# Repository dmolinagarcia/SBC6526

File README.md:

# SBC6526

SBC6526 is a single board computer built around A 65c02 CPU. It has been designed with a very specific purpose, that has defined both its name and its specs. I've been working for some time already on a MOS6526 (The famous CIA used in Commodore Computers) replica using 74xx logic series ICs. Testing was done on a real C64, but soon this prove to be a very limiting factor. So I begin working on a small SBC, designed entirely around the 6526, that should allow me to run as many tests, with no limitations at all.

The initial set of requisites was

* Continuosly variable clock, from 1MHz to as far as possible, in order to push my replica to its limits
* Clock Frequency Display. Useful, and should look very cool.
* No input at all. Program the ROM (more on this later) and just run a suite of tests for the 6526.
* Basic output.. Something like a 20x4 Character LCD will do.
* Easy, quick, and on board ROM programming. I will be modifiying the code continuosly, so this is very important.
* Include a 6522. Why not!? It can also be useful for the tests
* Include a socket for a 6526. Compatibility with old NMOS 6526 is not needed, although it would be nice.
* Allow testing of all 6526 pins. Ports, serial, /FLAG interrupt, etc
* Independent reset for 6526.

SBCv1 came to life, fulfilling this requirements. Howeever, after using it for some time, it show some weakness. SBCv1 has a 6522 and a 6526. A 4x40 LCD is used as display, driven by the 6526. This causes the display to blank when running some tests, and sometimes, crashed the LCD into an unrecoverable state, that requires a complete power down. This along some layout issues, forced the next revision. 

## Memory Map

0000 - 7FFF RAM
8000 - 87FF I/O BANK 0 - FREE
8800 - 8FFF I/O BANK 1 - CIA1
9000 - 97FF I/O BANK 2 - VIA
9800 - 9FFF I/O BANK 3 - CIAEXT
A000 - A7FF I/O BANK 4
A800 - AFFF I/O BANK 5
B000 - B7FF I/O BANK 6
B800 - BFFF I/O BANK 7
C000 - FFFF RAM

# v2
Being my first attempt at creating a SBC, v1 had many flaws. There were some pull-up resistors missing, the PCB layout was a mess, the bootstrap code was... well... unreadable to be honest. Moreover, the CAD tool I choose for v1, Eagle Cad, has a nasty licensing which is pulling away many users. I decided to make the transition to KiCAD for the v2. It's still a work in progress, and completely untested, but feel free to take a look if you like.

SBCv2 adds a second 6526. There's a 40 pin DIP socket that accepts both a MOS6526 or any modern replacement. Second 6526 connects over a 40 pin IDC that matches the 74HCT6526 interface. The LCD is now driven by the 6522, so both 6526 are 100% usable for testing. 

On SBCv1, TOD in the 6526 was used to determine clock speed. Now, a 60hz signal generated by the arduino goes into the 6522 for this purpose. SBC6526 can now startup and run with no 6526 connected at all. 

## BootStrap

The SBC6526 has no ROM. RAM exists between 0000-7FFF and C000-FFFF. As you know, the 6502 CPU needs the startup vectors to be present in the last segment of memory so, how does the SBC6526 boot?

An Arduino NANO handles the startup sequence. On startup, it brings BE low, disconnecting the 6502 from the address and data busses, and the R/W line. This also enables a pair of 8bit shift registers that handle from now on the address bus.

The RAM IC has 2 enable inputs. One is controled via the SBC Address Decoding logic, the other, directly by the ARDUINO. During BootStraping, RAMCE pulses with PHI2 (independent from the arduino) and the Arduino pulses CE line. This is a bit unorthodox and may cause some failures to write, if the arduino pulse happens when PHI2 is  high. This is handled by trying several times to write.

When the ROM image is written, BE is released, and the 6502 is resetted by the Arduino itself.

## KiCAD

Full schematic and PCB. The migration from EagleCAD to KiCAD has not been easy, as I was very much used to EagleCad. But the change as been worth the effort. 

## Firmware

With little architectural changes from v1, original firmware will need just some minor changes. Most important one, LCD screen is now driven by the 6522 instead of the 6526. Also, the internal clock measurement has to be done also with the 6522. Memory map will be the same, with just a second CIA added into an empty IO Slot.

## RamFlasher

Java code to upload memory image to SBC

## Changelog

### Unreleased

* Nothing

### v2.0.2 12-01-2022

* Minor fixes to routing
* Right VCC hole was slightly offset. Fixed
* Removed /CE from arduino to RAM. As RAMCE pulses with PHI, it's not necessary, and we leave /CE tied to GND.
* Fixed RAM footprint, as it was too wide. Improved routing.
* Added current limiting resistor to LCD Contrast
* Bootstrap and Firmware published. Not completed, but working.

### v2.0.1 29-12-2021

* Fixed a bug on LCD frequency meter footprint. Top row pads were reversed
* First draft of firmware, only for LOGISIM version
* Initial draft of bootstrap loader. Still not working.

### v2.0.0 10-19-2021

* First v2 release
* First PCB run

### v1.0.0 xx-xx-2020

* First and last v1 release
* It works, which is enough.

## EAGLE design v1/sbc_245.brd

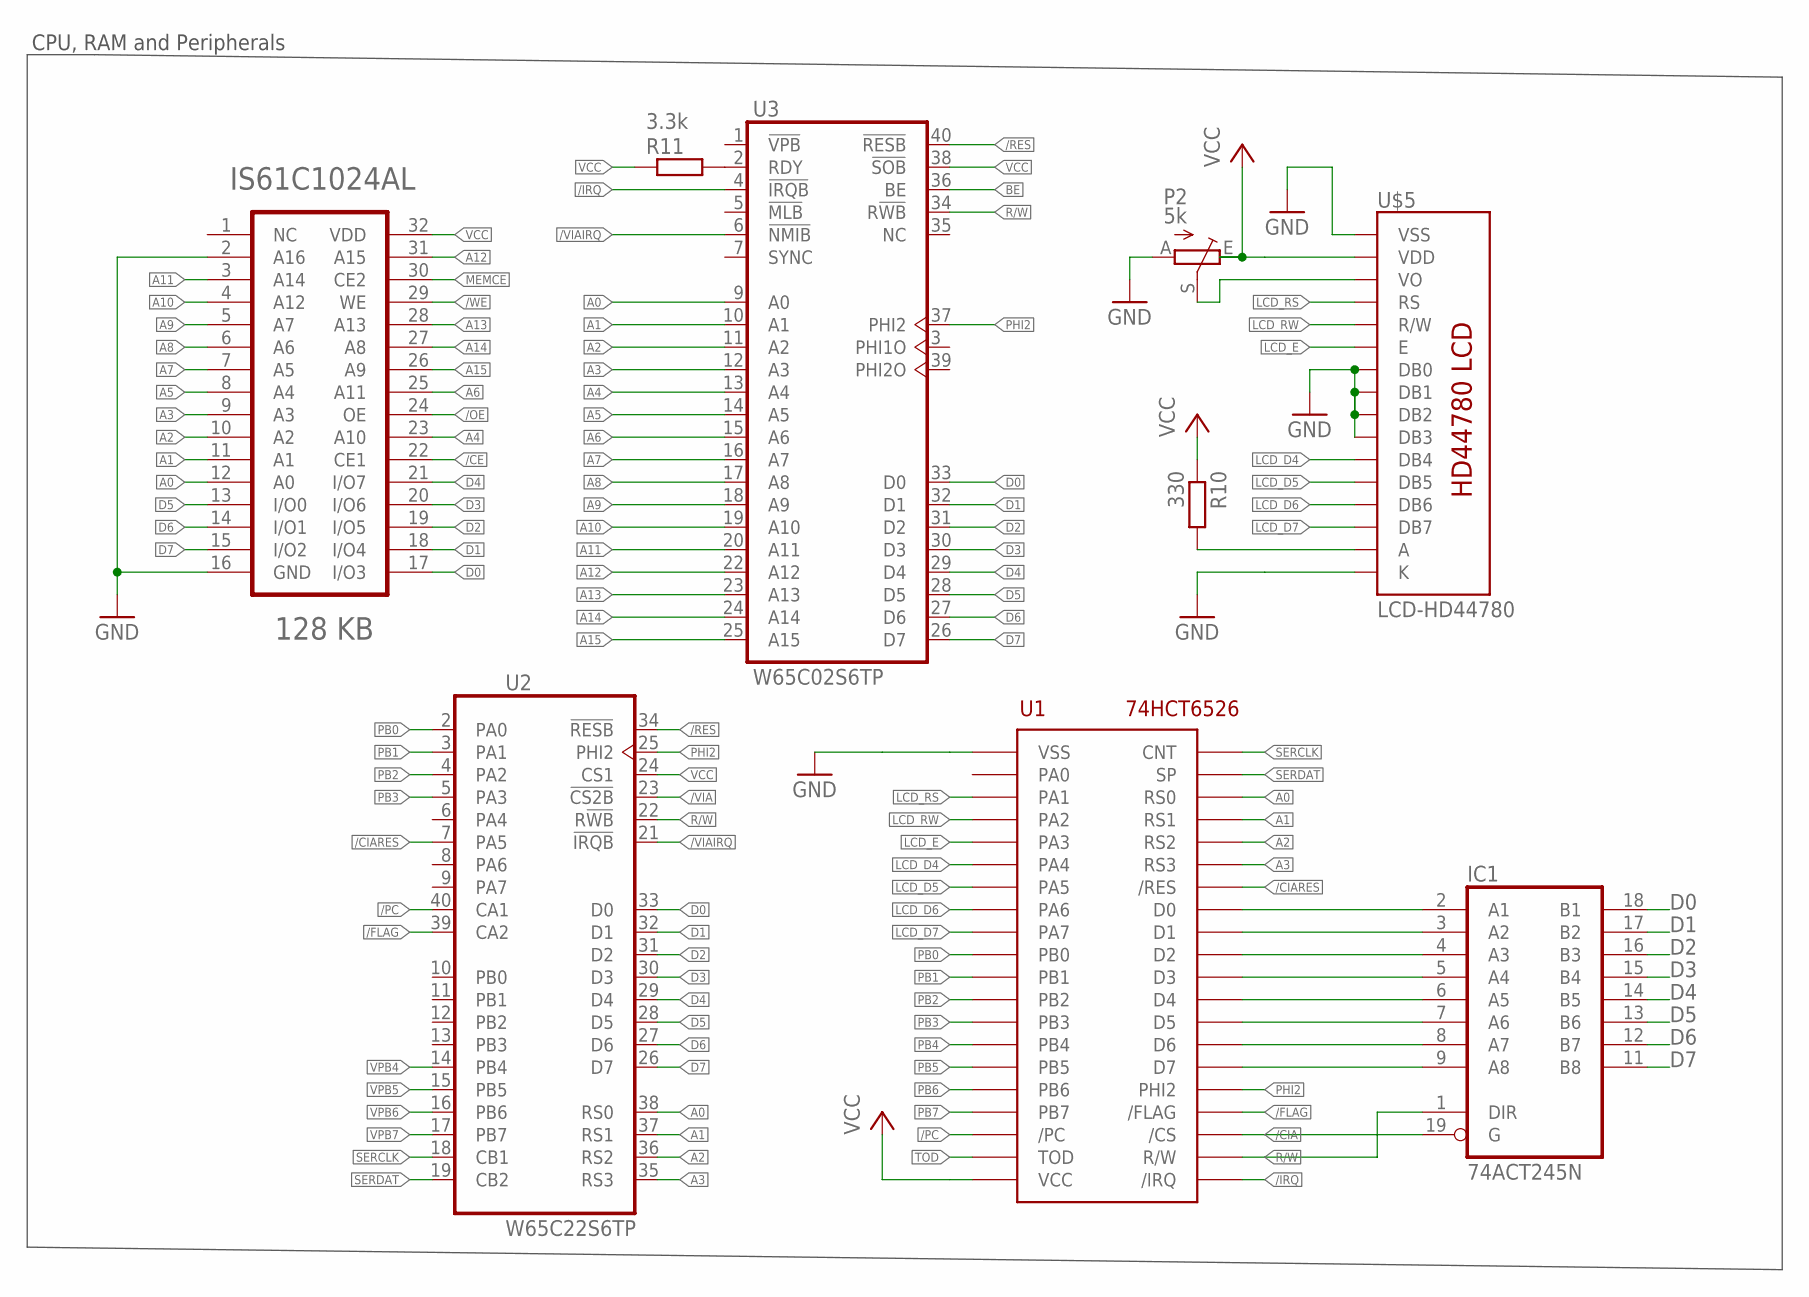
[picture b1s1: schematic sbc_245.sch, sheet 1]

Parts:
IC1: 74ACT245N; DIL20
P2: 5k; B64Y
R10: 330; R0805
R11: 3.3k; R0805
U1: 74HCT6526; DIP40
U2: W65C22S6TP; DIL40
U3: W65C02S6TP; DIL40
U4: IS61C1024AL-12JLI-TR; SOJ32/3
U$5: LCD-HD44780; LCD-20X4-4HOLES2X8

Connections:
/CE: U4.22 (CE1); also elsewhere on the board
/CIA: IC1.19 (G), U1.23 (/CS); also elsewhere on the board
/CIARES: U1.34 (/RES), U2.7 (PA5)
/FLAG: U1.24 (/FLAG), U2.39 (CA2)
/IRQ: U1.21 (/IRQ), U3.4 (!IRQB)
/OE: U4.24 (OE); also elsewhere on the board
/PC: U1.18 (/PC), U2.40 (CA1)
/RES: U2.34 (!RESB), U3.40 (!RESB); also elsewhere on the board
/VIA: U2.23 (!CS2B); also elsewhere on the board
/VIAIRQ: U2.21 (!IRQB), U3.6 (!NMIB)
/WE: U4.29 (WE); also elsewhere on the board
A0: U1.38 (RS0), U2.38 (RS0), U3.9 (A0), U4.12 (A0); also elsewhere on the board
A1: U1.37 (RS1), U2.37 (RS1), U3.10 (A1), U4.11 (A1); also elsewhere on the board
A2: U1.36 (RS2), U2.36 (RS2), U3.11 (A2), U4.10 (A2); also elsewhere on the board
A3: U1.35 (RS3), U2.35 (RS3), U3.12 (A3), U4.9 (A3); also elsewhere on the board
A4: U3.13 (A4), U4.23 (A10); also elsewhere on the board
A5: U3.14 (A5), U4.8 (A4); also elsewhere on the board
A6: U3.15 (A6), U4.25 (A11); also elsewhere on the board
A7: U3.16 (A7), U4.7 (A5); also elsewhere on the board
A8: U3.17 (A8), U4.6 (A6); also elsewhere on the board
A9: U3.18 (A9), U4.5 (A7); also elsewhere on the board
A10: U3.19 (A10), U4.4 (A12); also elsewhere on the board
A11: U3.20 (A11), U4.3 (A14); also elsewhere on the board
A12: U3.22 (A12), U4.31 (A15); also elsewhere on the board
A13: U3.23 (A13), U4.28 (A13); also elsewhere on the board
A14: U3.24 (A14), U4.27 (A8); also elsewhere on the board
A15: U3.25 (A15), U4.26 (A9); also elsewhere on the board
BE: U3.36 (BE); also elsewhere on the board
D0: IC1.18 (B1), U2.33 (D0), U3.33 (D0), U4.17 (I/O3); also elsewhere on the board
D1: IC1.17 (B2), U2.32 (D1), U3.32 (D1), U4.18 (I/O4); also elsewhere on the board
D2: IC1.16 (B3), U2.31 (D2), U3.31 (D2), U4.19 (I/O5); also elsewhere on the board
D3: IC1.15 (B4), U2.30 (D3), U3.30 (D3), U4.20 (I/O6); also elsewhere on the board
D4: IC1.14 (B5), U2.29 (D4), U3.29 (D4), U4.21 (I/O7); also elsewhere on the board
D5: IC1.13 (B6), U2.28 (D5), U3.28 (D5), U4.13 (I/O0); also elsewhere on the board
D6: IC1.12 (B7), U2.27 (D6), U3.27 (D6), U4.14 (I/O1); also elsewhere on the board
D7: IC1.11 (B8), U2.26 (D7), U3.26 (D7), U4.15 (I/O2); also elsewhere on the board
GND: IC1.10 (GND), P2.A, U1.1 (VSS), U4.2 (A16), U4.16 (GND), U$5.P$1 (VSS), U$5.P$7 (DB0), U$5.P$8 (DB1), U$5.P$9 (DB2), U$5.P$10 (DB3), U$5.P$16 (K); also elsewhere on the board
LCDA: R10.2, U$5.P$15 (A)
LCD_D4: U1.6 (PA4), U$5.P$11 (DB4)
LCD_D5: U1.7 (PA5), U$5.P$12 (DB5)
LCD_D6: U1.8 (PA6), U$5.P$13 (DB6)
LCD_D7: U1.9 (PA7), U$5.P$14 (DB7)
LCD_E: U1.5 (PA3), U$5.P$6 (E)
LCD_RS: U1.3 (PA1), U$5.P$4 (RS)
LCD_RW: U1.4 (PA2), U$5.P$5 (R/W)
MEMCE: U4.30 (CE2); also elsewhere on the board
unnamed: IC1.2 (A1), U1.33 (D0)
unnamed: IC1.3 (A2), U1.32 (D1)
unnamed: IC1.4 (A3), U1.31 (D2)
unnamed: IC1.5 (A4), U1.30 (D3)
unnamed: IC1.6 (A5), U1.29 (D4)
unnamed: P2.S, U$5.P$3 (VO)
unnamed: IC1.7 (A6), U1.28 (D5)
unnamed: IC1.8 (A7), U1.27 (D6)
unnamed: R11.2, U3.2 (RDY)
unnamed: IC1.9 (A8), U1.26 (D7)
PB0: U1.10 (PB0), U2.2 (PA0); also elsewhere on the board
PB1: U1.11 (PB1), U2.3 (PA1); also elsewhere on the board
PB2: U1.12 (PB2), U2.4 (PA2); also elsewhere on the board
PB3: U1.13 (PB3), U2.5 (PA3); also elsewhere on the board
PB4: U1.14 (PB4); also elsewhere on the board
PB5: U1.15 (PB5); also elsewhere on the board
PB6: U1.16 (PB6); also elsewhere on the board
PB7: U1.17 (PB7); also elsewhere on the board
PHI2: U1.25 (PHI2), U2.25 (PHI2), U3.37 (PHI2); also elsewhere on the board
R/W: IC1.1 (DIR), U1.22 (R/W), U2.22 (R!WB), U3.34 (R!WB); also elsewhere on the board
SERCLK: U1.40 (CNT), U2.18 (CB1)
SERDAT: U1.39 (SP), U2.19 (CB2)
TOD: U1.19 (TOD); also elsewhere on the board
VCC: IC1.20 (VCC), P2.E, R10.1, R11.1, U1.20 (VCC), U2.24 (CS1), U3.38 (!SOB), U4.32 (VDD), U$5.P$2 (VDD); also elsewhere on the board
VPB4: U2.14 (PB4); also elsewhere on the board
VPB5: U2.15 (PB5); also elsewhere on the board
VPB6: U2.16 (PB6); also elsewhere on the board
VPB7: U2.17 (PB7); also elsewhere on the board

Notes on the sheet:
CPU, RAM and Peripherals

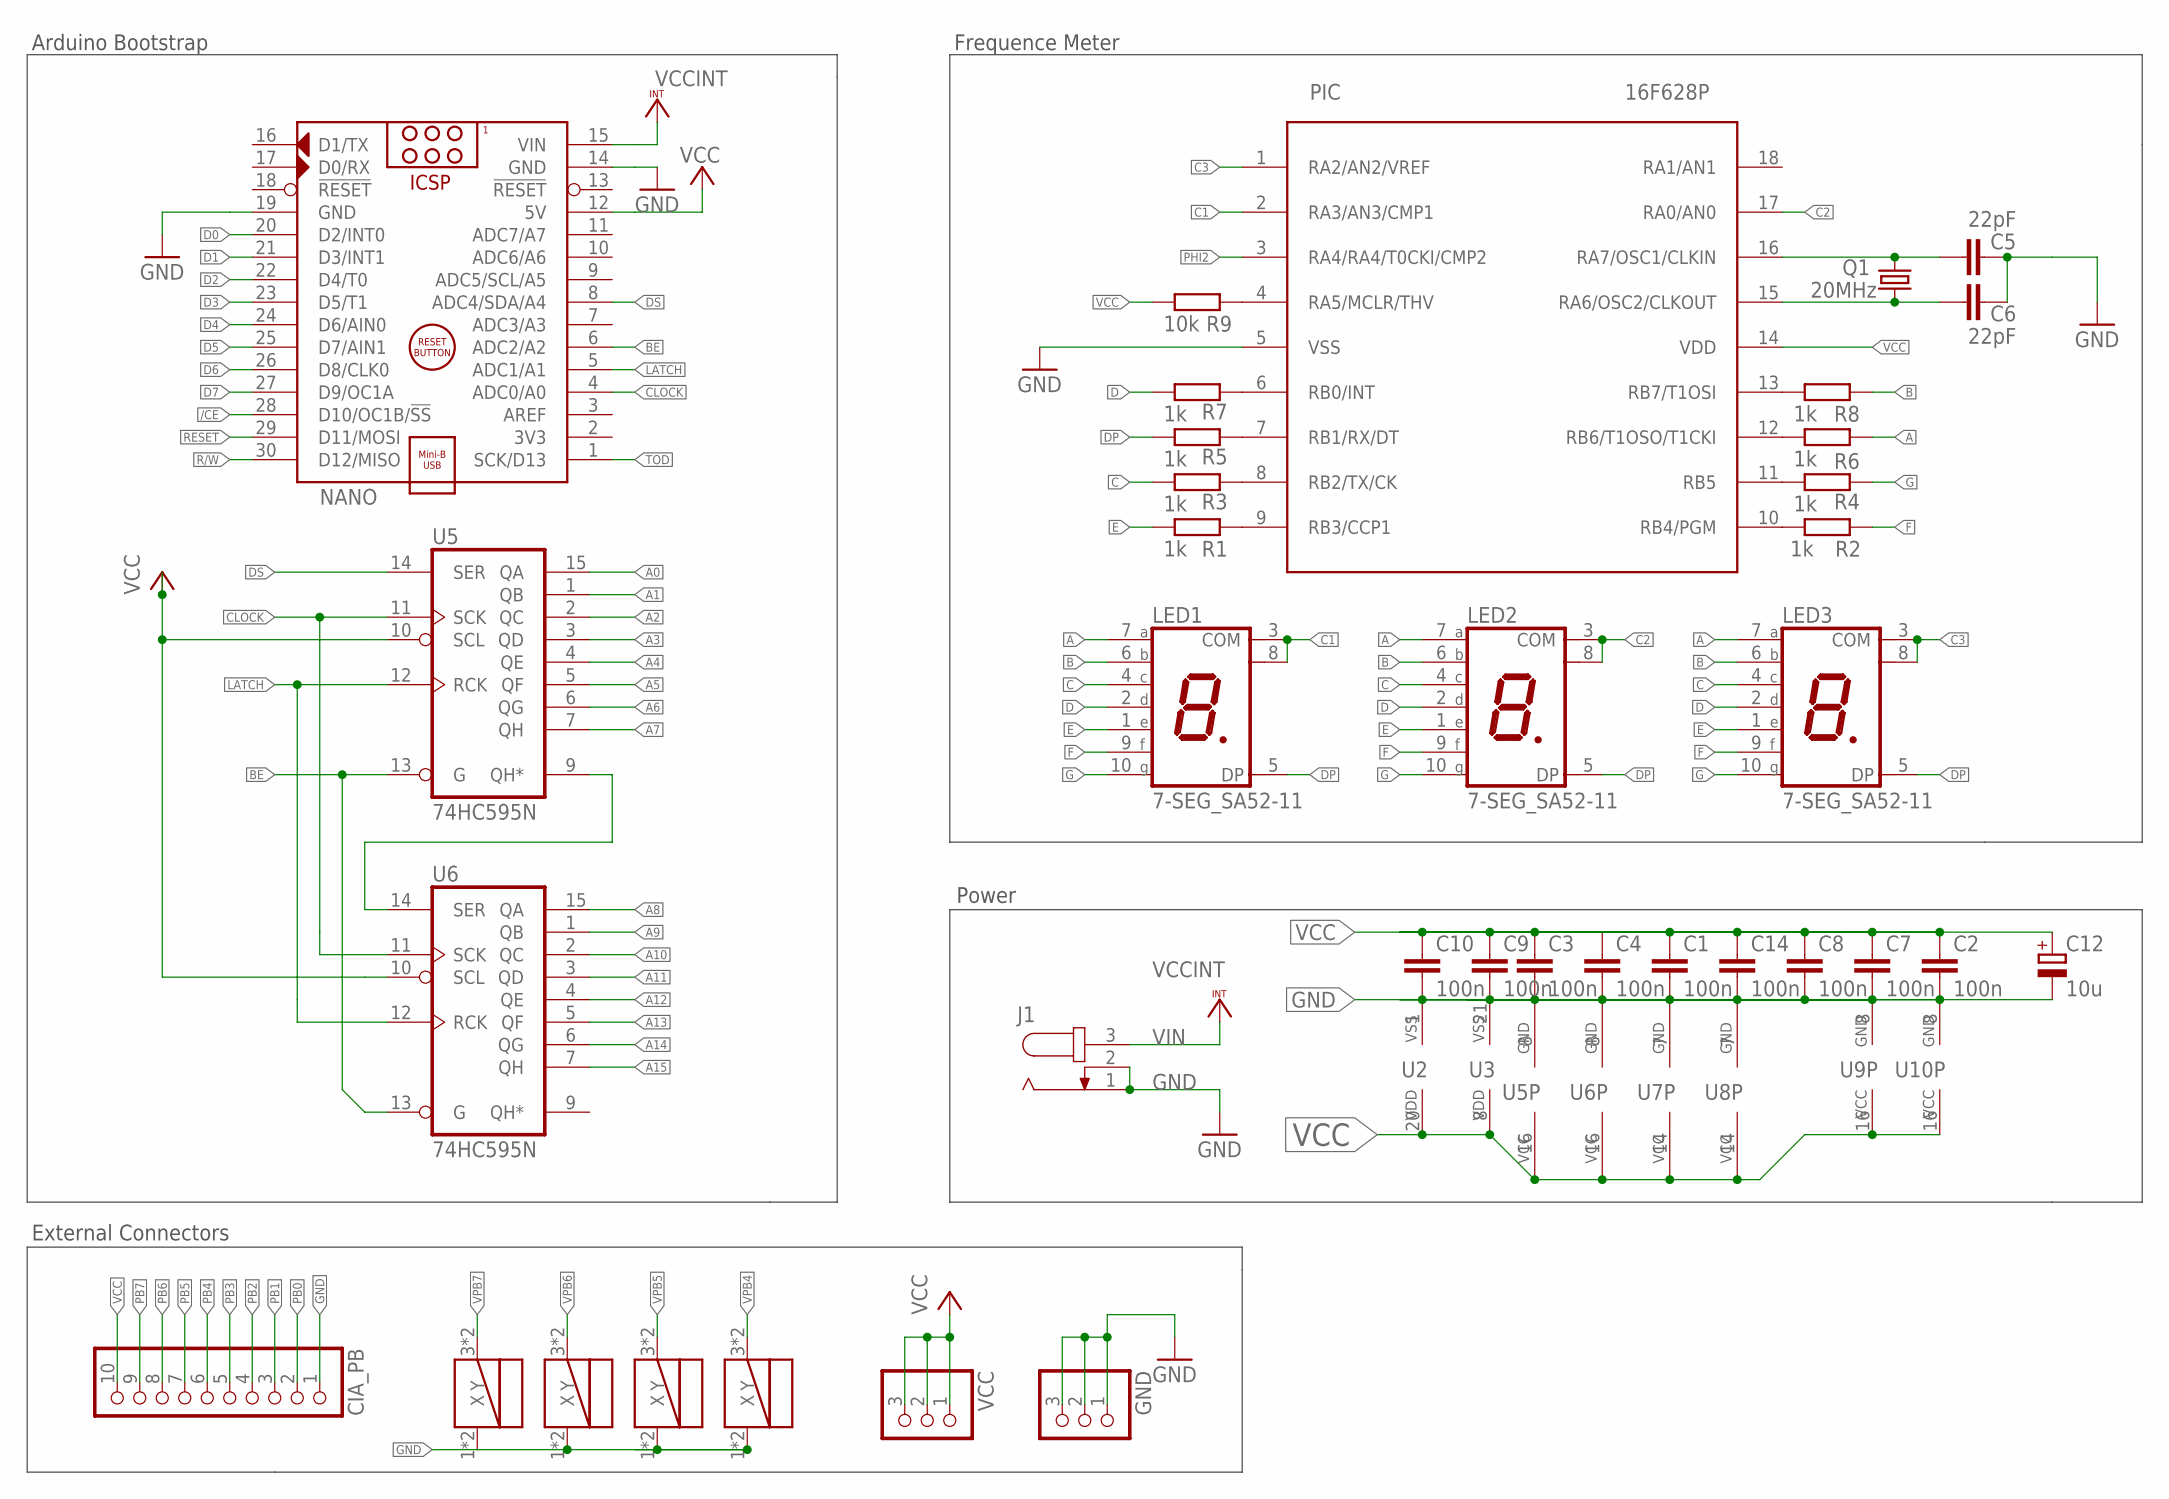
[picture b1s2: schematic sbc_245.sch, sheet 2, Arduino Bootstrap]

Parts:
C1, C2, C3, C4, C7, C8, C9, C10, C14: 100n; C0805
C5, C6: 22pF; C025-025X050
C12: 10u; B45181A
CIA_PB: PINHD-1X10; 1X10
GND: PINHD-1X3; 1X03
J1: JACK-PLUG0; SPC4077
LED1, LED2, LED3: 7-SEG_SA52-11; SA52-11
NANO: ARDUINO_NANO
PIC: 16F628P; DIL18
Q1: 20MHz; HC18U-V
R1, R2, R3, R4, R5, R6, R7, R8: 1k; 0207/7
R9: 10k; R0805
U2: W65C22S6TP; DIL40
U3: W65C02S6TP; DIL40
U5, U6: 74HC595N; SO16
U7: 74AC74D; SO14
U8: 74AC14D; SO14
U9: 74AC139D; SO16
U10: 74AC138D; SO16
U$1, U$2, U$3, U$4: TSA451G90-250
VCC: PINHD-1X3; 1X03

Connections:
/CE: NANO.28 (D10/OC1B/!SS); also elsewhere on the board
A: LED1.7 (A), LED2.7 (A), LED3.7 (A), R6.2
A0: U5.15 (QA); also elsewhere on the board
A1: U5.1 (QB); also elsewhere on the board
A2: U5.2 (QC); also elsewhere on the board
A3: U5.3 (QD); also elsewhere on the board
A4: U5.4 (QE); also elsewhere on the board
A5: U5.5 (QF); also elsewhere on the board
A6: U5.6 (QG); also elsewhere on the board
A7: U5.7 (QH); also elsewhere on the board
A8: U6.15 (QA); also elsewhere on the board
A9: U6.1 (QB); also elsewhere on the board
A10: U6.2 (QC); also elsewhere on the board
A11: U6.3 (QD); also elsewhere on the board
A12: U6.4 (QE); also elsewhere on the board
A13: U6.5 (QF); also elsewhere on the board
A14: U6.6 (QG); also elsewhere on the board
A15: U6.7 (QH); also elsewhere on the board
B: LED1.6 (B), LED2.6 (B), LED3.6 (B), R8.2
BE: NANO.6 (ADC2/A2), U5.13 (G), U6.13 (G); also elsewhere on the board
C: LED1.4 (C), LED2.4 (C), LED3.4 (C), R3.1
C1: LED1.3 (COM), LED1.8 (COM), PIC.2 (RA3/AN3/CMP1)
C2: LED2.3 (COM), LED2.8 (COM), PIC.17 (RA0/AN0)
C3: LED3.3 (COM), LED3.8 (COM), PIC.1 (RA2/AN2/VREF)
CLOCK: NANO.4 (ADC0/A0), U5.11 (SCK), U6.11 (SCK)
D: LED1.2 (D), LED2.2 (D), LED3.2 (D), R7.1
D0: NANO.20 (D2/INT0); also elsewhere on the board
D1: NANO.21 (D3/INT1); also elsewhere on the board
D2: NANO.22 (D4/T0); also elsewhere on the board
D3: NANO.23 (D5/T1); also elsewhere on the board
D4: NANO.24 (D6/AIN0); also elsewhere on the board
D5: NANO.25 (D7/AIN1); also elsewhere on the board
D6: NANO.26 (D8/CLK0); also elsewhere on the board
D7: NANO.27 (D9/OC1A); also elsewhere on the board
DP: LED1.5 (DP), LED2.5 (DP), LED3.5 (DP), R5.1
DS: NANO.8 (ADC4/SDA/A4), U5.14 (SER)
E: LED1.1 (E), LED2.1 (E), LED3.1 (E), R1.1
F: LED1.9 (F), LED2.9 (F), LED3.9 (F), R2.1
G: LED1.10 (G), LED2.10 (G), LED3.10 (G), R4.2
GND: C1.2, C2.2, C3.2, C4.2, C5.2, C6.2, C7.2, C8.2, C9.2, C10.2, C12.-, C14.2, CIA_PB.1, GND.1, GND.2, GND.3, J1.1, J1.2, NANO.14 (GND), NANO.19 (GND), PIC.5 (VSS), U2.1 (VSS), U3.21 (VSS), U5.8 (GND), U6.8 (GND), U7.7 (GND), U8.7 (GND), U9.8 (GND), U10.8 (GND), U$1.1 (X), U$1.2 (X), U$2.1 (X), U$2.2 (X), U$3.1 (X), U$3.2 (X), U$4.1 (X), U$4.2 (X); also elsewhere on the board
LATCH: NANO.5 (ADC1/A1), U5.12 (RCK), U6.12 (RCK)
unnamed: U5.9 (QH*), U6.14 (SER)
unnamed: PIC.6 (RB0/INT), R7.2
unnamed: PIC.7 (RB1/RX/DT), R5.2
unnamed: PIC.8 (RB2/TX/CK), R3.2
unnamed: PIC.9 (RB3/CCP1), R1.2
unnamed: PIC.10 (RB4/PGM), R2.2
unnamed: PIC.11 (RB5), R4.1
unnamed: PIC.12 (RB6/T1OSO/T1CKI), R6.1
unnamed: PIC.13 (RB7/T1OSI), R8.1
unnamed: C5.1, PIC.16 (RA7/OSC1/CLKIN), Q1.2
unnamed: C6.1, PIC.15 (RA6/OSC2/CLKOUT), Q1.1
unnamed: PIC.4 (RA5/MCLR/THV), R9.2
PB0: CIA_PB.2; also elsewhere on the board
PB1: CIA_PB.3; also elsewhere on the board
PB2: CIA_PB.4; also elsewhere on the board
PB3: CIA_PB.5; also elsewhere on the board
PB4: CIA_PB.6; also elsewhere on the board
PB5: CIA_PB.7; also elsewhere on the board
PB6: CIA_PB.8; also elsewhere on the board
PB7: CIA_PB.9; also elsewhere on the board
PHI2: PIC.3 (RA4/RA4/T0CKI/CMP2); also elsewhere on the board
R/W: NANO.30 (D12/MISO); also elsewhere on the board
RESET: NANO.29 (D11/MOSI); also elsewhere on the board
TOD: NANO.1 (SCK/D13); also elsewhere on the board
VCC: C1.1, C2.1, C3.1, C4.1, C7.1, C8.1, C9.1, C10.1, C12.+, C14.1, CIA_PB.10, NANO.12 (5V), PIC.14 (VDD), R9.1, U2.20 (VDD), U3.8 (VDD), U5.10 (SCL), U5.16 (VCC), U6.10 (SCL), U6.16 (VCC), U7.14 (VCC), U8.14 (VCC), U9.16 (VCC), U10.16 (VCC), VCC.1, VCC.2, VCC.3; also elsewhere on the board
VIN: J1.3, NANO.15 (VIN)
VPB4: U$4.3 (Y), U$4.4 (Y); also elsewhere on the board
VPB5: U$3.3 (Y), U$3.4 (Y); also elsewhere on the board
VPB6: U$2.3 (Y), U$2.4 (Y); also elsewhere on the board
VPB7: U$1.3 (Y), U$1.4 (Y); also elsewhere on the board

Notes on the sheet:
Arduino Bootstrap
Frequence Meter
Power
External Connectors

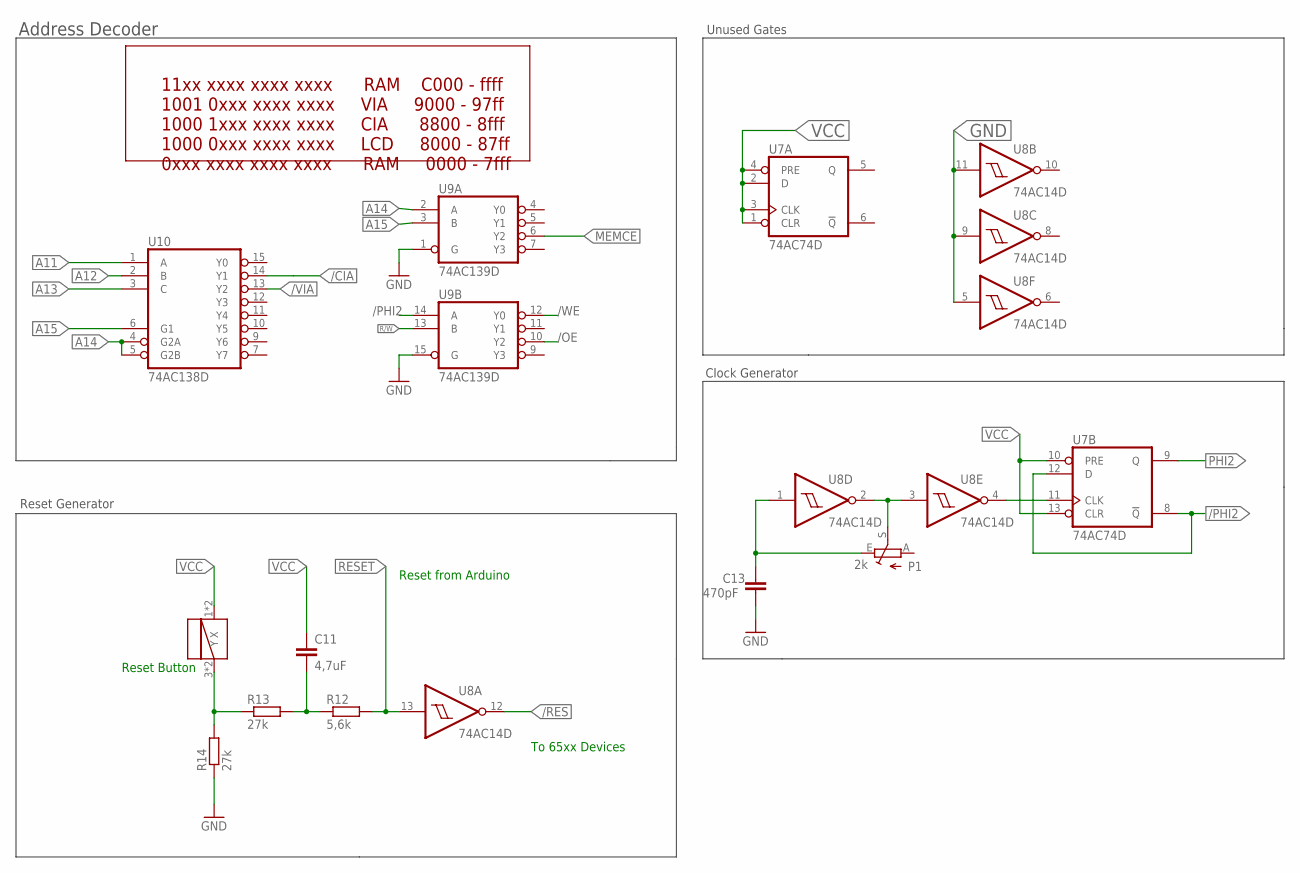
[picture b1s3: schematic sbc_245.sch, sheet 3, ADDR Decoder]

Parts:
C11: 4,7uF; C0805
C13: 470pF; C0805
P1: 2k; B64Y
R12: 5,6k; R0805
R13, R14: 27k; R0805
SW1: TSA451G90-250
U7: 74AC74D; SO14
U8: 74AC14D; SO14
U9: 74AC139D; SO16
U10: 74AC138D; SO16

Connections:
/CIA: U10.14 (Y1); also elsewhere on the board
/OE: U9.10 (Y2); also elsewhere on the board
/PHI2: U7.8 (!Q), U7.12 (D), U9.14 (A)
/RES: U8.12 (O); also elsewhere on the board
/VIA: U10.13 (Y2); also elsewhere on the board
/WE: U9.12 (Y0); also elsewhere on the board
A11: U10.1 (A); also elsewhere on the board
A12: U10.2 (B); also elsewhere on the board
A13: U10.3 (C); also elsewhere on the board
A14: U9.2 (A), U10.4 (G2A), U10.5 (G2B); also elsewhere on the board
A15: U9.3 (B), U10.6 (G1); also elsewhere on the board
GND: C13.2, R14.1, U8.5 (I), U8.9 (I), U8.11 (I), U9.1 (G), U9.15 (G); also elsewhere on the board
MEMCE: U9.6 (Y2); also elsewhere on the board
unnamed: P1.S, U8.2 (O), U8.3 (I)
unnamed: U7.11 (CLK), U8.4 (O)
unnamed: C13.1, P1.E, U8.1 (I)
unnamed: R13.1, R14.2, SW1.3 (Y), SW1.4 (Y)
unnamed: C11.2, R12.1, R13.2
PHI2: U7.9 (Q); also elsewhere on the board
R/W: U9.13 (B); also elsewhere on the board
RESET: R12.2, U8.13 (I); also elsewhere on the board
VCC: C11.1, SW1.1 (X), SW1.2 (X), U7.1 (CLR), U7.2 (D), U7.3 (CLK), U7.4 (PRE), U7.10 (PRE), U7.13 (CLR); also elsewhere on the board

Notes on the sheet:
11xx xxxx xxxx xxxx RAM C000 - ffff 1001 0xxx xxxx xxxx VIA 9000 - 97ff 1000 1xxx xxxx xxxx CIA 8800 - 8fff 1000 0xxx xxxx xxxx LCD 8000 - 87ff 0xxx xxxx xxxx xxxx RAM 0000 - 7fff
Reset Button
Reset from Arduino
To 65xx Devices
Address Decoder
Unused Gates
Clock Generator
Reset Generator

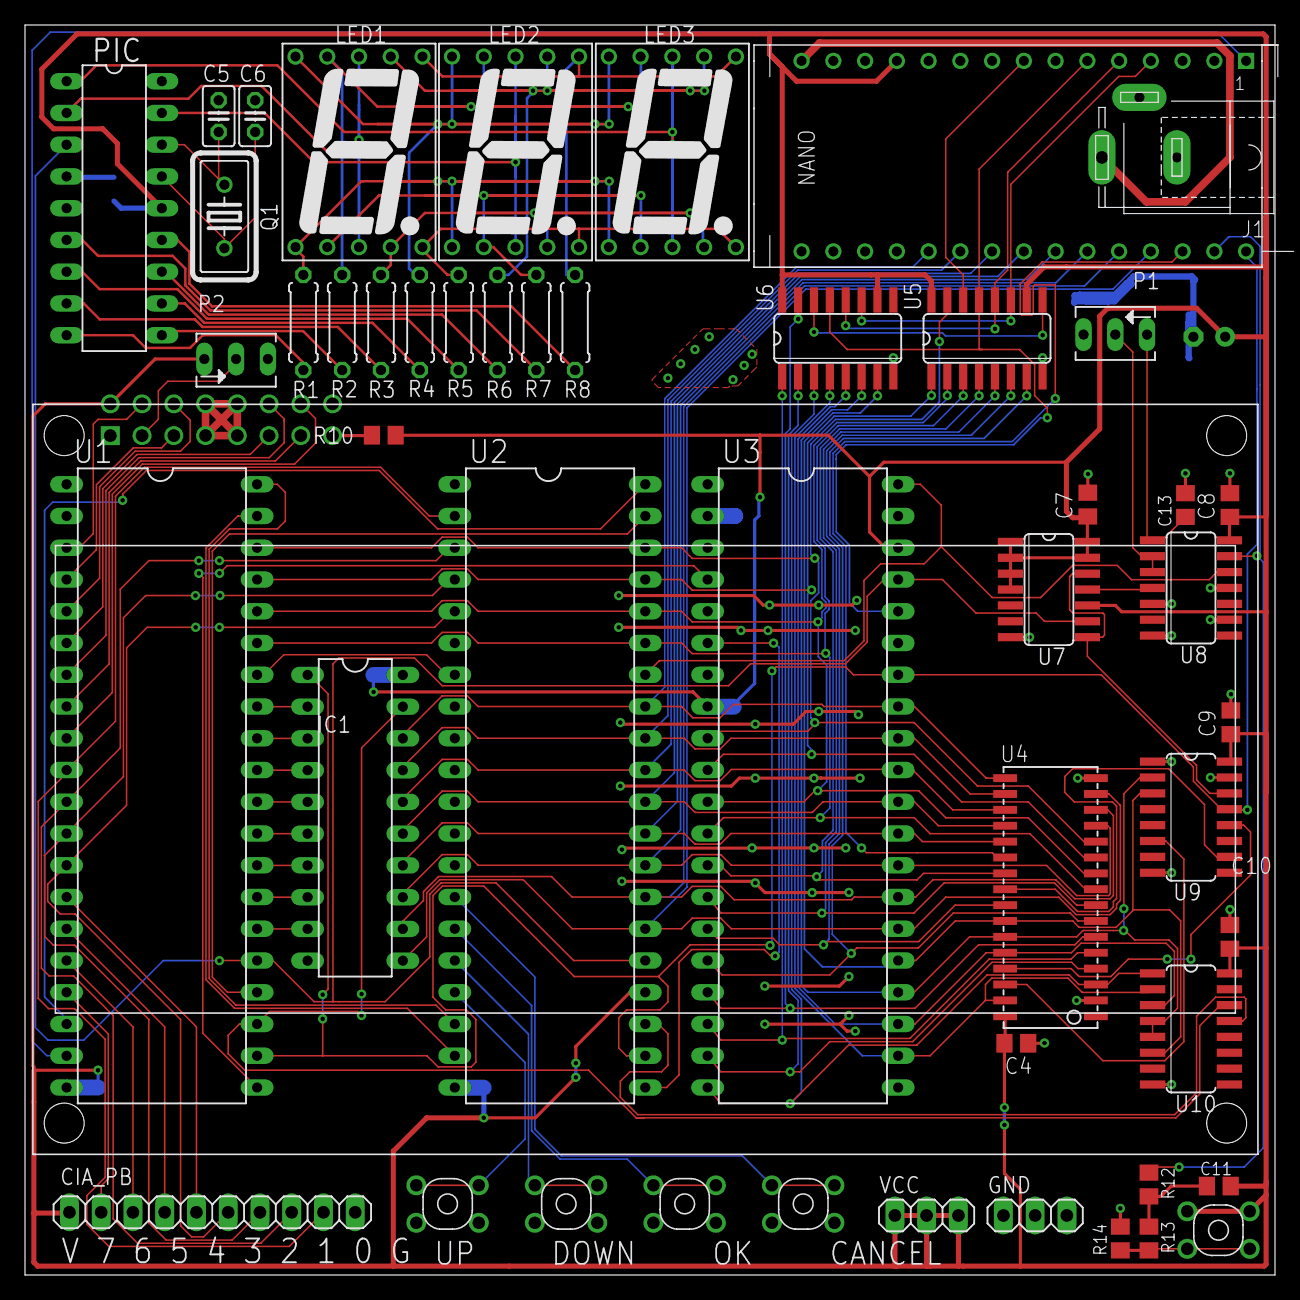
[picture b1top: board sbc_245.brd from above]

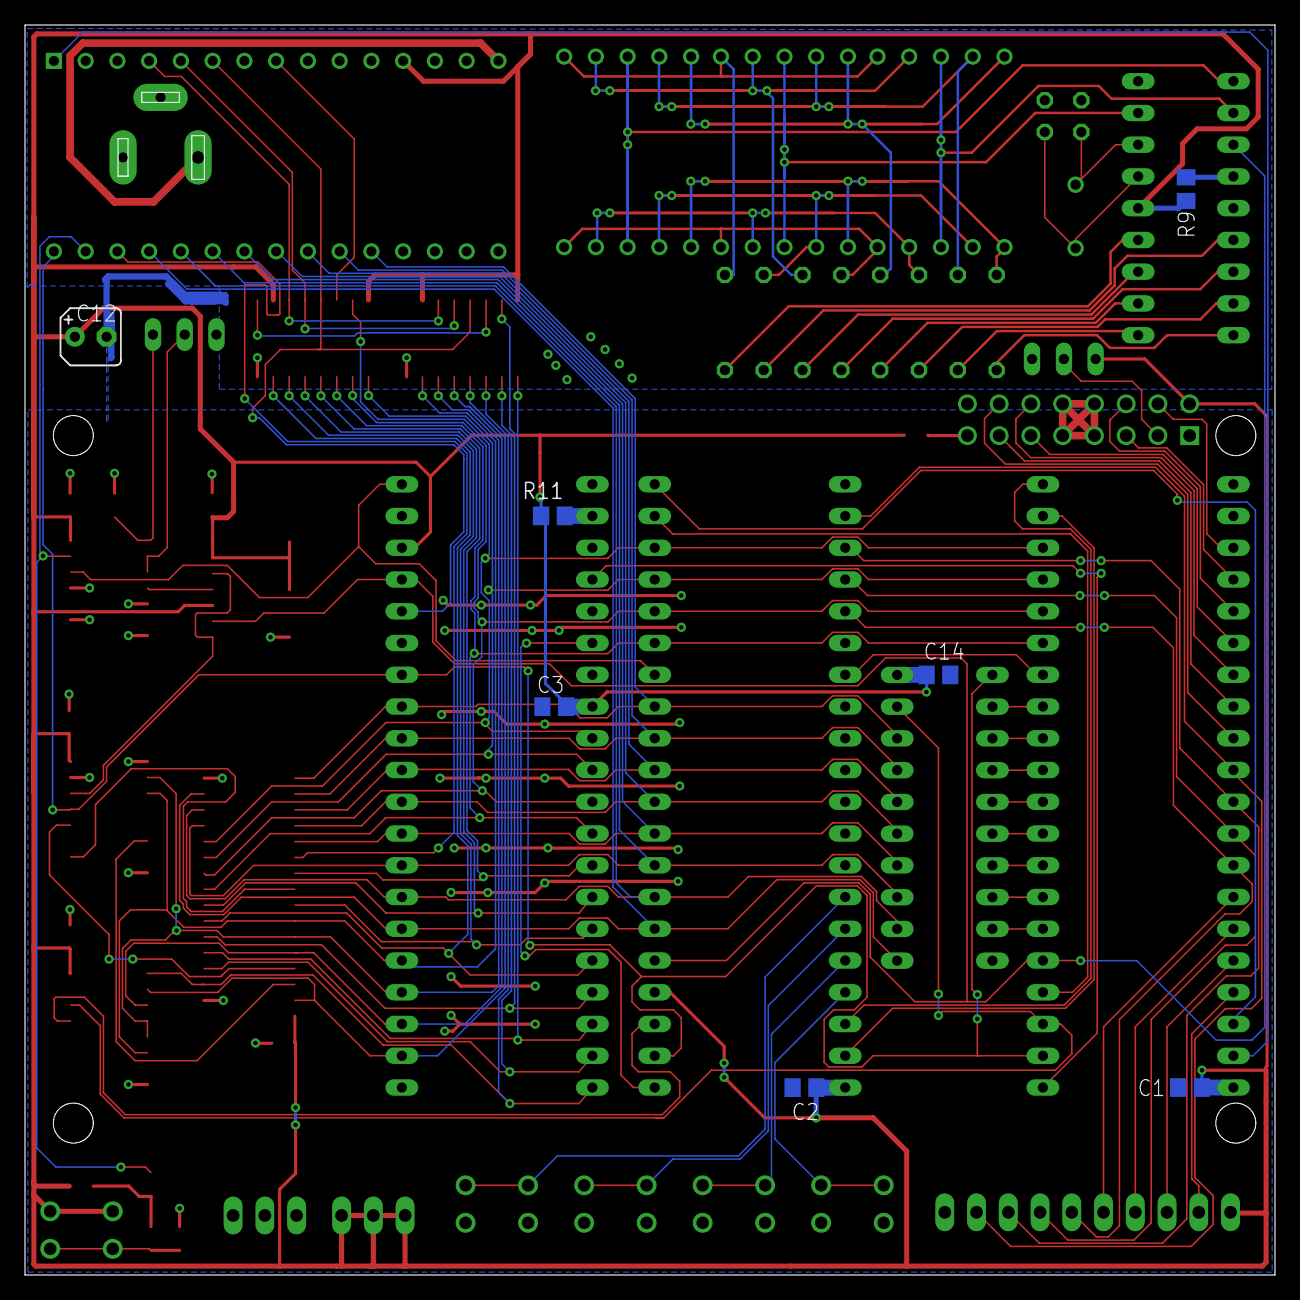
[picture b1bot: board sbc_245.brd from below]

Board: 2 copper layers, 100.0 x 100.0 mm, 57 parts (7 on the bottom side), 108 nets.

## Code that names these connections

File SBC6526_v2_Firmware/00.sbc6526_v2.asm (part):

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									// LCD RW   Low (Write)
									// LCD E    High
			lda #$FF
			sta VIA_DDRA			// PA0     : ciaReset
									// PA1-PA7 : LCD
									// PA      : All Outputs

									// Enable TOD from arduino
			lda VIA_DDRB
			ora #%00000001    
			sta VIA_DDRB			// PB0 as output, (TODENABLE) others unchanged
	
			lda VIA_PRTB
			and #%11111110
			sta VIA_PRTB			// PB0 Low, others, unchanged

			pla
			rts
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			sta IRQ_COUNTER				// into interrupt counter

			lda #%01000000
			sta VIA_ACR					// TIMER1 continuous. PB7 off, 
										// shift register off, pb latches off

			lda #$20
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
					lda VIA_PRTB
					ora #%00000001
					sta VIA_PRTB			// PB0 high, others, unchanged
	
					lda VIA_DDRB
					ora #%01000000    
					sta VIA_DDRB			// PB6 as output, (TOD) others unchanged

					pla
					rts
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
					lda VIA_DDRB
					and #%10111111
					sta VIA_DDRB			// PB6 as input, (TOD) others unchanged

					lda VIA_PRTB
					and #%11111110
					sta VIA_PRTB			// PB0 Low, others, unchanged	

					pla
					rts		
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											// Ticks TOD X times
					lda VIA_PRTB
					ora #%01000000
					sta VIA_PRTB			// PB6 high, others, unchanged
					and #%10111111
					sta VIA_PRTB			// PB6 low, others, unchanged	
					dex 
					bne tickTodFromVia					
					rts
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// Send instruction in A HI nibble to lcd
			pha

			ora #$01 				// CIARES a 1 que es PA0
			ora #$08 				// Enable a 1
									// Envia instrucción al LCD. 
									// Bits 4-7 del acumulador
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
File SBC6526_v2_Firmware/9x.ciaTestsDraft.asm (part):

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tick2:		
				lda VIA_PRTB
				ora #%00000010
				sta VIA_PRTB			// PB1 high, others, unchanged

				and #%11111101
				sta VIA_PRTB			// PB1 low, others, unchanged


				jsr krnShortDelay
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
//////////////////////////////////////
stopTODticker:
				// PB0 en la via se debe poner HIGH (es tod enable)
				lda VIA_DDRB
				ora #%00000001    
				sta VIA_DDRB			// PB0 as output, (TODENABLE) others unchanged

				lda VIA_PRTB
				ora #%00000001
				sta VIA_PRTB			// PB0 high, others, unchanged

				lda VIA_DDRB
				ora #%00000010    
				sta VIA_DDRB			// PB1 as output, (TOD) others unchanged

				lda #'0'
				sta $7002
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  ldy #$00
  sty CIA2_TAHI
forceloada:
  ldy #%00010011				// 00010111 : FL PULSE PB6ON START CONT PHI2
  sty CIA2_CRGA

loadb:
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  ldy #$00
  sty CIA2_TBHI
forceloadb:
  ldy #%01011011				// 01011011 : FL PULSE PB7 ON START O.S TAunderflows					
  sty CIA2_CRGB

waitforbunder:					// Wait until timerb has stopped
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					ldy #$00
					sty CIA2_TAHI			// CIA2 TA set to 0x0010
forceloada:
					ldy #%00010011			// 00010111 : FL PULSE PB6ON START CONT PHI2
					sty CIA2_CRGA
loadb:
					ldy #$00
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					ldy #$00
					sty CIA2_TBHI
forceloadb:
					ldy #%01011011			// 01011011 : FL PULSE PB7 ON START O.S TAunderflows
					sty CIA2_CRGB

waitfornmi:
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
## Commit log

2020-11-16 Re-creation
    Repository has been recreated to add a new (still WIP) v2 version.
2020-11-16 Rename README.md to README_v1.md
2020-11-16 Create README_v2.md
    Readme for v2
2020-11-26 Update README_v2.md
    Fixed typos
2020-11-26 Delete README.md
    Duplicate
2020-11-27 All nets verified
    All nets have been verified against all design. Even though v2 is not tested yet, at least, the schematic is correct.
2020-12-11 new revision - dual 6526
    new revision - dual 6526
2020-12-15 Changing to Dual CIA
2021-09-15 PCB Tweaks
    Tracks optimized.
    SMD components moved to top layer.
2021-10-01 v1.0
2021-10-01 Move to v2
2021-10-01 v2.0
    Production ready
2021-10-02 v2.0 layout optimization
2021-10-06 Minor
2021-10-17 Minor fixes in PCB, and ready for production
2021-10-18 Fixes to mounting holes.
2021-10-27 Initial deploy of v2 firmware
    Small run test in logisim completed.
2021-11-05 Updates to firmware
2021-11-30 Firmware Updates
2021-12-29 Fixed Freq. Meter footprint
    Frequency meter footprint was wrong. Top row was reversed.
    Minor additions to bootstrap and firmware.
2022-01-09 Fixes
    * Minor fixes to routing
    * Right VCC hole was slightly offset. Fixed
    * Removed /CE from arduino to RAM. As RAMCE pulses with PHI, it's not necessary, and we leave /CE tied to GND.
    * Fixed RAM footprint, as it was too wide. Improved routing.
    * Added current limiting resistor to LCD Contrast
2022-01-12 Uploaded firmware v2.0.2
2022-03-20 mid Backup
2022-07-30 PullUps con SERCLOCK and SERDAT
2022-08-13 incremental check
2022-12-23 Firmware
2023-01-08 Start of IRQ Testing
    Also, TODENABLE in the arduino is weird
2023-01-08 ciaTest divided into different files. Also, IRQ tests mostly done
2023-01-09 Fixed TODENABLE
2023-01-11 ICR tests completed
2023-01-12 Register Detection
2023-01-12 Initial register detectin. Pending test jump
2023-01-13 ICR apparently completed!
2023-02-13 Code changes
2023-02-13 Firmware dev
2023-03-31 incremental changes
2023-05-07 Firmware changes
